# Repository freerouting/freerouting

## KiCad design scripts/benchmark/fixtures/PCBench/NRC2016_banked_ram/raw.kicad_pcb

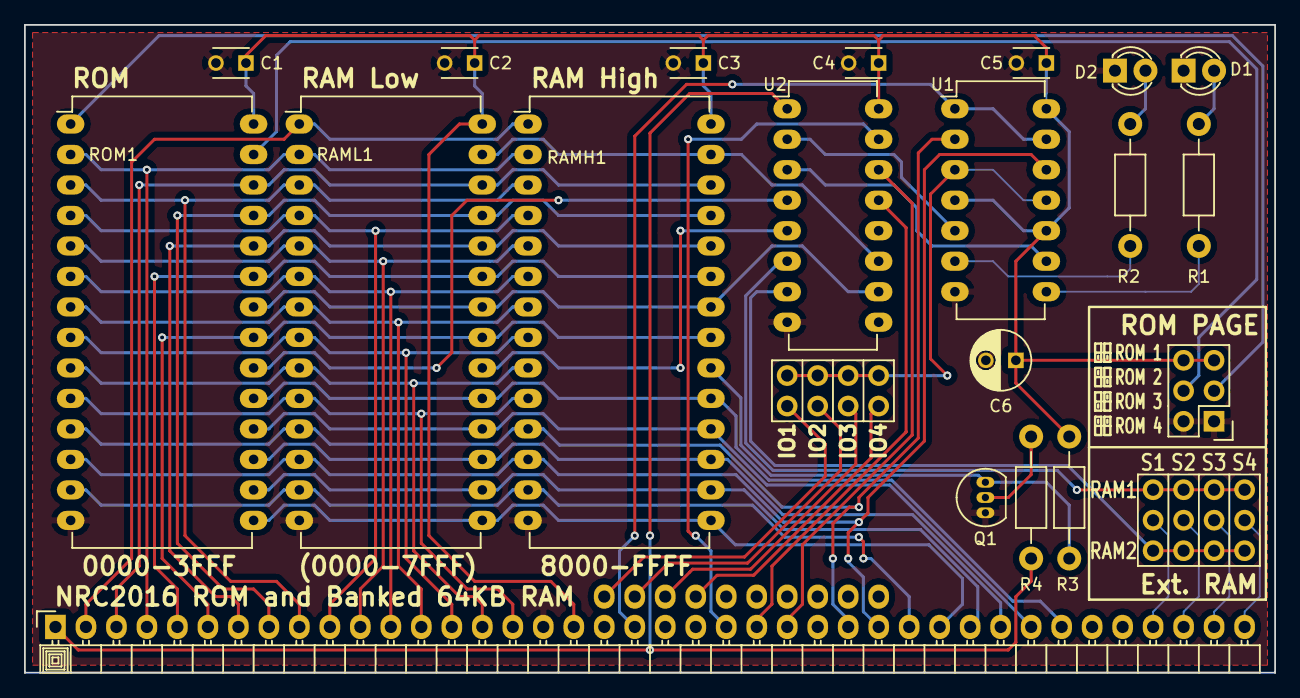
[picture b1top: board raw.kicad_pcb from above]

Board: 2 copper layers, 104.1 x 54.0 mm, 24 parts (0 on the bottom side), 55 nets.

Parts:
C1, C2, C3, C4, C5: C; C_Disc_D3_P2.5
C6: CP; C_Radial_D5_L11_P2.5
D1, D2: LED; LED-3MM
LOGO1: BackLogo; nrc2016_top_logo_1600
P1: IO_BUS_PINS; Pin_Header_Angled_1x10_nrc2016
P2: CONN_02X04; Pin_Header_Straight_2x04_nrc2016
P3: CONN_02X03; Pin_Header_Straight_2x03
P4: Z80_BUS_PINS; Pin_Header_Angled_1x40_nrc2016
Q1: Q_NPN_EBC; TO-92_Inline_Narrow_Oval
R1, R2, R3, R4: R; Resistor_Horizontal_RM10mm
RAMH1: 62256; DIP-28_W15.24mm_LongPads
RAML1: 62256; DIP-28_W15.24mm_LongPads
RAMSEL1: CONN_04x03; ramsel_pins
ROM1: 27C512; DIP-28_W15.24mm_LongPads
U1: 74LS74; DIP-14_W7.62mm_LongPads
U2: 74LS139; DIP-16_W7.62mm_LongPads

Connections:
/A0: P4.16, RAMH1.10, RAML1.10, ROM1.10
/A1: P4.15, RAMH1.9, RAML1.9, ROM1.9
/A2: P4.14, RAMH1.8, RAML1.8, ROM1.8
/A3: P4.13, RAMH1.7, RAML1.7, ROM1.7
/A4: P4.12, RAMH1.6, RAML1.6, ROM1.6
/A5: P4.11, RAMH1.5, RAML1.5, ROM1.5
/A6: P4.10, RAMH1.4, RAML1.4, ROM1.4
/A7: P4.9, RAMH1.3, RAML1.3, ROM1.3
/A8: P4.8, RAMH1.25, RAML1.25, ROM1.25
/A9: P4.7, RAMH1.24, RAML1.24, ROM1.24
/A10: P4.6, RAMH1.21, RAML1.21, ROM1.21
/A11: P4.5, RAMH1.23, RAML1.23, ROM1.23
/A12: P4.4, RAMH1.2, RAML1.2, ROM1.2
/A13: P4.3, RAMH1.26, RAML1.26, ROM1.26
/A14: P4.2, RAMH1.1, RAML1.1
/A15: P4.1, R4.1, U2.1
/D0: P4.27, RAMH1.11, RAML1.11, ROM1.11, U1.2
/D1: P4.28, RAMH1.12, RAML1.12, ROM1.12, U1.12
/D2: P4.29, RAMH1.13, RAML1.13, ROM1.13
/D3: P4.30, RAMH1.15, RAML1.15, ROM1.15
/D4: P4.31, RAMH1.16, RAML1.16, ROM1.16
/D5: P4.32, RAMH1.17, RAML1.17, ROM1.17
/D6: P4.33, RAMH1.18, RAML1.18, ROM1.18
/D7: P4.34, RAMH1.19, RAML1.19, ROM1.19
/~EXT_RAM1: RAMSEL1.1, RAMSEL1.2, RAMSEL1.3, RAMSEL1.4, U2.6
/~EXT_RAM2: RAMSEL1.9, RAMSEL1.10, RAMSEL1.11, RAMSEL1.12, U2.7
/~MREQ: P4.23, U2.15
/~RAMH_CS: Q1.3, R3.2, RAMH1.20
/~RAML_CS: RAML1.20, U2.5
/~RD: P4.25, U2.14
/~READ: RAMH1.22, RAML1.22, ROM1.22, U2.10
/~RESET: P4.20, U1.1, U1.13
/~ROM_CS: ROM1.20, U2.4
/~WR: P4.24, U2.13
/~WRITE: RAMH1.27, RAML1.27, U2.11
GND: C1.2, C2.2, C3.2, C4.2, C5.2, C6.2, D1.1, D2.1, P3.1, P3.2, P4.17, Q1.1, RAMH1.14, RAML1.14, ROM1.14, U1.7, U2.8
unnamed: D1.2, R1.2
unnamed: D2.2, R2.2
unnamed: P1.1, P2.1
unnamed: P1.2, P2.3
unnamed: P1.3, P2.5
unnamed: P1.4, P2.7
unnamed: P2.2, P2.4, P2.6, P2.8, U1.3, U1.11
unnamed: P3.3, ROM1.1
unnamed: P3.4, ROM1.27
unnamed: P4.37, RAMSEL1.8
unnamed: P4.38, RAMSEL1.7
unnamed: P4.39, RAMSEL1.6
unnamed: P4.40, RAMSEL1.5
unnamed: Q1.2, R4.2
unnamed: R1.1, U1.8
unnamed: R2.1, U1.6
unnamed: U1.5, U2.2
unnamed: U1.9, U2.3
VCC: C1.1, C2.1, C3.1, C4.1, C5.1, C6.1, P3.5, P3.6, P4.18, R3.1, RAMH1.28, RAML1.28, ROM1.28, U1.4, U1.10, U1.14, U2.16

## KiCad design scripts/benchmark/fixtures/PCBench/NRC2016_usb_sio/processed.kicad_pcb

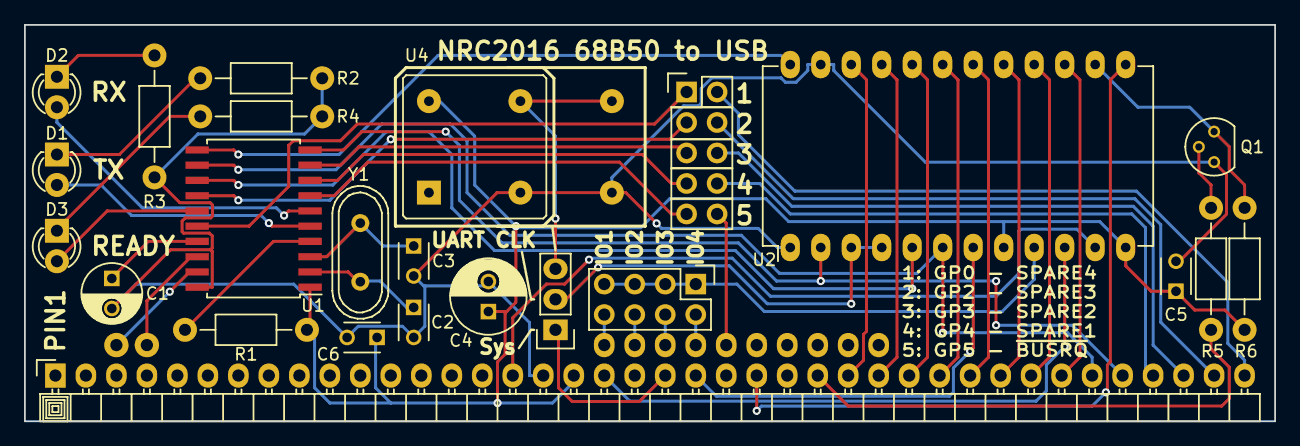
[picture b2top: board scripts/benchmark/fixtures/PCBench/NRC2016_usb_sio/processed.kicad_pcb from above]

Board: 2 copper layers, 104.1 x 33.0 mm, 27 parts (0 on the bottom side), 51 nets.

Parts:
C1: 1uF; C_Radial_D5_L6_P2.5
C2, C3: 22pF; C_Disc_D3_P2.5
C4: 10uF; C_Radial_D6.3_L11.2_P2.5
C5, C6: 100nF; C_Disc_D3_P2.5
CON1: USB; Pin_Header_Angled_1x02_nrc2016
D1: TX LED; LED-3MM
D2: RX LED; LED-3MM
D3: USB RDY; LED-3MM
JP1: JUMPER3; Pin_Header_Straight_1x03
LOGO1: BackLogo; nrc2016_top_logo_1600
P1: Z80_BUS_PINS; Pin_Header_Angled_1x40_nrc2016
P2: IO_BUS_PINS; Pin_Header_Angled_1x10_nrc2016
P3: CONN_02X05; Pin_Header_Straight_2x05
P4: CONN_02X04; Pin_Header_Straight_2x04
Q1: Q_NPN_EBC; TO-92_Molded_Narrow
R1, R5: 10K; Resistor_Horizontal_RM10mm
R2, R3, R4: 220; Resistor_Horizontal_RM10mm
R6: 2K2; Resistor_Horizontal_RM10mm
U1: MCP2200; SOIC-20W_7.5x12.8mm_Pitch1.27mm
U2: 68B50; DIP-24_W15.24mm_LongPads
U4: 1.8432MHz; OSC_MULTIPACKAGE_DIP
Y1: 12MHz; Crystal_HC49-U_Vertical

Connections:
/A0: P1.16, U2.11
/D0: P1.27, U2.22
/D1: P1.28, U2.21
/D2: P1.29, U2.20
/D3: P1.30, U2.19
/D4: P1.31, U2.18
/D5: P1.32, U2.17
/D6: P1.33, U2.16
/D7: P1.34, U2.15
/ENA: Q1.3, R6.2, U2.14
/GP0: P3.1, U1.16
/GP2: P3.3, U1.14
/GP3: P3.5, U1.9
/GP4: P3.7, U1.8
/GP5: P3.9, U1.7
/RX: P1.36, U1.10, U2.2
/S1: P1.37, P3.8
/S2: P1.38, P3.6
/S3: P1.39, P3.4
/S4: P1.40, P3.2
/TX: P1.35, U1.12, U2.6
/~BUSRQ: P2.5, P3.10
/~CLK: JP1.1, P1.21
/~INT: P1.22, U2.7
/~IORQ: P1.26, R5.2
/~IOSEL: P4.1, P4.3, P4.5, P4.7, U2.9
/~M1: P1.19, U2.10
/~WR: P1.24, U2.13
GND: C1.2, C2.2, C3.2, C4.2, C5.2, C6.2, P1.17, Q1.1, R2.1, R3.1, R4.1, U1.20, U2.1, U2.23, U4.GND
unnamed: C1.1, U1.17
unnamed: C2.1, U1.2, Y1.1
unnamed: C3.1, U1.3, Y1.2
unnamed: CON1.1, U1.19
unnamed: CON1.2, U1.18
unnamed: D1.1, R2.2
unnamed: D1.2, U1.5
unnamed: D2.1, R3.2
unnamed: D2.2, U1.6
unnamed: D3.1, R4.2
unnamed: D3.2, U1.15
unnamed: JP1.2, U2.3, U2.4
unnamed: JP1.3, U4.OUT
unnamed: P2.1, P4.8
unnamed: P2.2, P4.6
unnamed: P2.3, P4.4
unnamed: P2.4, P4.2
unnamed: Q1.2, R5.1
unnamed: R1.2, U1.4
unnamed: U1.11, U2.24
unnamed: U1.13, U2.5
VCC: C4.1, C5.1, C6.1, P1.18, R1.1, R6.1, U1.1, U2.8, U2.12, U4.VCC

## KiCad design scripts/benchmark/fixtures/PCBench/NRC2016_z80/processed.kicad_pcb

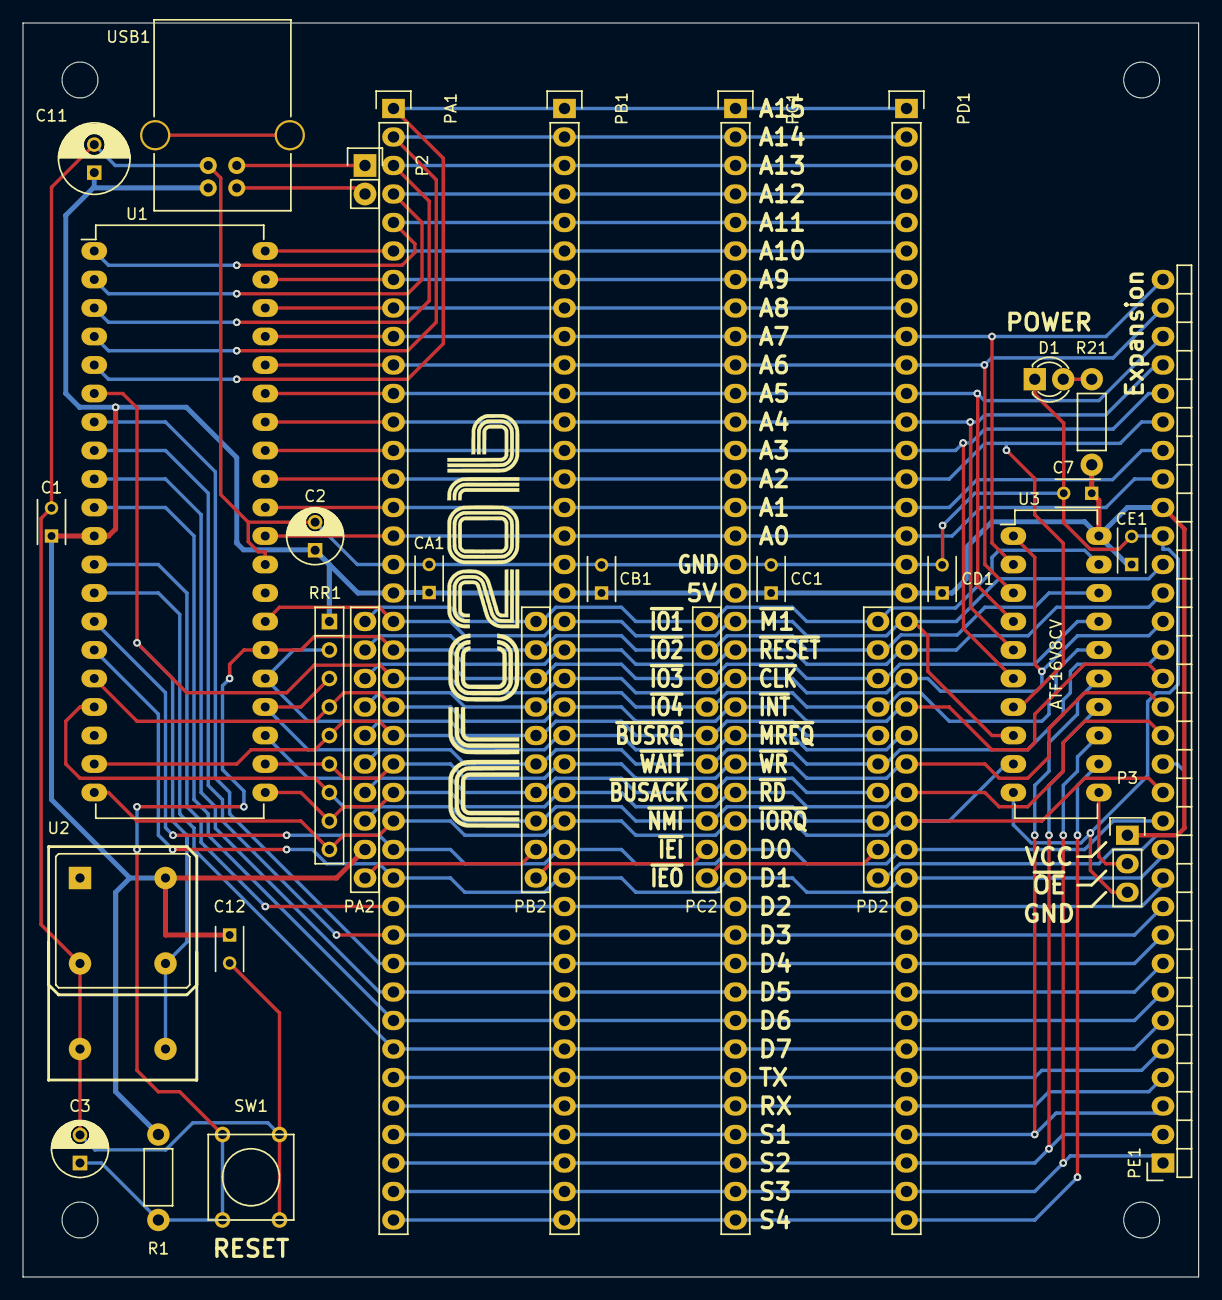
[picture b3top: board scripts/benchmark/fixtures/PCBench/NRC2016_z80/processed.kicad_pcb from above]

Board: 2 copper layers, 104.8 x 111.8 mm, 37 parts (0 on the bottom side), 56 nets.

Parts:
C1, C7, C12: 100n; C_Rect_L4_W2.5_P2.5
C2, C3: 1uF; C_Radial_D5_L6_P2.5
C11: 10u; C_Radial_D6.3_L11.2_P2.5
CA1: 100n; C_Rect_L4_W2.5_P2.5
CB1: 100n; C_Rect_L4_W2.5_P2.5
CC1: 100n; C_Rect_L4_W2.5_P2.5
CD1: 100n; C_Rect_L4_W2.5_P2.5
CE1: 100n; C_Rect_L4_W2.5_P2.5
D1: LED; LED-3MM
LOGO1: FrontLogo; nrc2016_top_logo_1600
LOGO2: BackLogo; nrc2016_bottom_logo_600_v2
MH1, MH2, MH3, MH4: MH_3mm; MountingHole_3.2mm_M3
P2: USB_SOCKET; Socket_Strip_Straight_1x02
P3: Jumper; Pin_Header_Straight_1x03
PA1: Z80_BUS_SOCKET; Socket_Strip_Straight_1x40
PA2: IO_BUS_SOCKET; Socket_Strip_Straight_1x10_NRC2016
PB1: Z80_BUS_SOCKET; Socket_Strip_Straight_1x40
PB2: IO_BUS_SOCKET; Socket_Strip_Straight_1x10_NRC2016
PC1: Z80_BUS_SOCKET; Socket_Strip_Straight_1x40
PC2: IO_BUS_SOCKET; Socket_Strip_Straight_1x10_NRC2016
PD1: Z80_BUS_SOCKET; Socket_Strip_Straight_1x40
PD2: IO_BUS_SOCKET; Socket_Strip_Straight_1x10_NRC2016
PE1: EXPANSION_SOCKET; Socket_Strip_Angled_1x32_nrc2016
R1: 10K; Resistor_Horizontal_RM7mm
R21: 220; Resistor_Horizontal_RM7mm
RR1: RR8; Resistor_Array_SIP8
SW1: RESET; SW_PUSH_SMALL
U1: Z80CPU; DIP-40_W15.24mm_LongPads
U2: DIP_OSCILLATOR; OSC_MULTIPACKAGE_DIP
U3: ATF16V8CV; DIP-20_W7.62mm_LongPads
USB1: USB_B

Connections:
/A0: PA1.16, PB1.16, PC1.16, PD1.16, PE1.25, U1.30
/A1: PA1.15, PB1.15, PC1.15, PD1.15, PE1.26, U1.31
/A2: PA1.14, PB1.14, PC1.14, PD1.14, PE1.27, U1.32, U3.7
/A3: PA1.13, PB1.13, PC1.13, PD1.13, PE1.28, U1.33, U3.6
/A4: PA1.12, PB1.12, PC1.12, PD1.12, PE1.29, U1.34, U3.5
/A5: PA1.11, PB1.11, PC1.11, PD1.11, PE1.30, U1.35, U3.4
/A6: PA1.10, PB1.10, PC1.10, PD1.10, PE1.31, U1.36, U3.3
/A7: PA1.9, PB1.9, PC1.9, PD1.9, PE1.32, U1.37, U3.2
/A8: PA1.8, PB1.8, PC1.8, PD1.8, U1.38
/A9: PA1.7, PB1.7, PC1.7, PD1.7, U1.39
/A10: PA1.6, PB1.6, PC1.6, PD1.6, U1.40
/A11: PA1.5, PB1.5, PC1.5, PD1.5, U1.1
/A12: PA1.4, PB1.4, PC1.4, PD1.4, U1.2
/A13: PA1.3, PB1.3, PC1.3, PD1.3, U1.3
/A14: PA1.2, PB1.2, PC1.2, PD1.2, U1.4
/A15: PA1.1, PB1.1, PC1.1, PD1.1, U1.5
/Card Slots/Expansion/IEI: PD2.10, PE1.15
/Card Slots/PortB/IEI: PA2.10, PB2.9
/Card Slots/PortC/IEI: PB2.10, PC2.9
/Card Slots/PortD/IEI: PC2.10, PD2.9
/Card Slots/RX: PA1.36, PB1.36, PC1.36, PD1.36, PE1.4
/Card Slots/S1: PA1.37, PB1.37, PC1.37, PD1.37, PE1.3, U3.15
/Card Slots/S2: PA1.38, PB1.38, PC1.38, PD1.38, PE1.2, U3.14
/Card Slots/S3: PA1.39, PB1.39, PC1.39, PD1.39, PE1.1, U3.13
/Card Slots/S4: PA1.40, PB1.40, PC1.40, PD1.40, U3.12
/Card Slots/TX: PA1.35, PB1.35, PC1.35, PD1.35, PE1.5
/Card Slots/~IOSEL0: PA2.1, PB2.1, PC2.1, PD2.1, U3.19
/Card Slots/~IOSEL1: PA2.2, PB2.2, PC2.2, PD2.2, U3.18
/Card Slots/~IOSEL2: PA2.3, PB2.3, PC2.3, PD2.3, U3.17
/Card Slots/~IOSEL3: PA2.4, PB2.4, PC2.4, PD2.4, U3.16
/D0: PA1.27, PB1.27, PC1.27, PD1.27, PE1.13, U1.14
/D1: PA1.28, PB1.28, PC1.28, PD1.28, PE1.12, U1.15
/D2: PA1.29, PB1.29, PC1.29, PD1.29, PE1.11, U1.12
/D3: PA1.30, PB1.30, PC1.30, PD1.30, PE1.10, U1.8
/D4: PA1.31, PB1.31, PC1.31, PD1.31, PE1.9, U1.7
/D5: PA1.32, PB1.32, PC1.32, PD1.32, PE1.8, U1.9
/D6: PA1.33, PB1.33, PC1.33, PD1.33, PE1.7, U1.10
/D7: PA1.34, PB1.34, PC1.34, PD1.34, PE1.6, U1.13
/~BUSACK: PA2.7, PB2.7, PC2.7, PD2.7, U1.23
/~BUSRQ: PA2.5, PB2.5, PC2.5, PD2.5, RR1.2, U1.25
/~CLK: PA1.21, PB1.21, PC1.21, PD1.21, PE1.20, U1.6, U2.OUT, U3.1
/~INT: PA1.22, PB1.22, PC1.22, PD1.22, PE1.18, RR1.4, U1.16
/~IORQ: PA1.26, PB1.26, PC1.26, PD1.26, PE1.14, RR1.9, U1.20, U3.9
/~M1: PA1.19, PB1.19, PC1.19, PD1.19, PE1.22, U1.27, U3.8
/~MREQ: PA1.23, PB1.23, PC1.23, PD1.23, RR1.5, U1.19
/~NMI: PA2.8, PB2.8, PC2.8, PD2.8, RR1.7, U1.17
/~RD: PA1.25, PB1.25, PC1.25, PD1.25, PE1.16, RR1.8, U1.21
/~RESET: C3.1, PA1.20, PB1.20, PC1.20, PD1.20, PE1.21, R1.1, SW1.2, U1.26
/~WAIT: PA2.6, PB2.6, PC2.6, PD2.6, PE1.19, RR1.3, U1.24
/~WR: PA1.24, PB1.24, PC1.24, PD1.24, PE1.17, RR1.6, U1.22
GND: C1.2, C2.2, C3.2, C7.2, C11.2, C12.2, CA1.2, CB1.2, CC1.2, CD1.2, CE1.2, D1.1, P3.3, PA1.17, PB1.17, PC1.17, PD1.17, PE1.23, SW1.1, U1.29, U2.GND, U3.10, USB1.4
unnamed: D1.2, R21.2
unnamed: P2.1, USB1.3
unnamed: P2.2, USB1.2
unnamed: P3.2, U3.11
VCC: C1.1, C2.1, C7.1, C11.1, C12.1, CA1.1, CB1.1, CC1.1, CD1.1, CE1.1, P3.1, PA1.18, PA2.9, PB1.18, PC1.18, PD1.18, PE1.24, R1.2, R21.1, RR1.1, U1.11, U2.VCC, U3.20, USB1.1
